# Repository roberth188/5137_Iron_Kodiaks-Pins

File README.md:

# 5137_Iron_Kodiaks-Pins
The team circuit board pins files, including both the schematic/board and Gerber files.
Contact me if you have any questions.

To order new boards, go to [dirtyPCBs](http://dirtypcbs.com/) and upload all of the Gerber files (the files that don't end in either .sch or .brd. Make sure to select 2 layer, the 5x5 cm size, the proper quantity, red color, 1.6mm thickness, ENIG Coating, no stencil, Regular processing, shipping to United States, and DHL China works very well. This will make the boards exactly like they were ordered before. 

Contact me about ordering the components - they vary considerably with what is in stock, so they will need to be found again.

Board file images were rendered with the fabulous ZofzPCB tool (available free online) and the colors were adjusted to accurately represent the ENIG plating over the pads of the red PCBS (for the team's cardinal and gold colors).

</img> </img> 

Yes, the trace that goes through the switch in that pad is unintentional but, as that connection is shorted, anyways, when it is turned off, it electrically has no impact. It can be safely and completely ignored.

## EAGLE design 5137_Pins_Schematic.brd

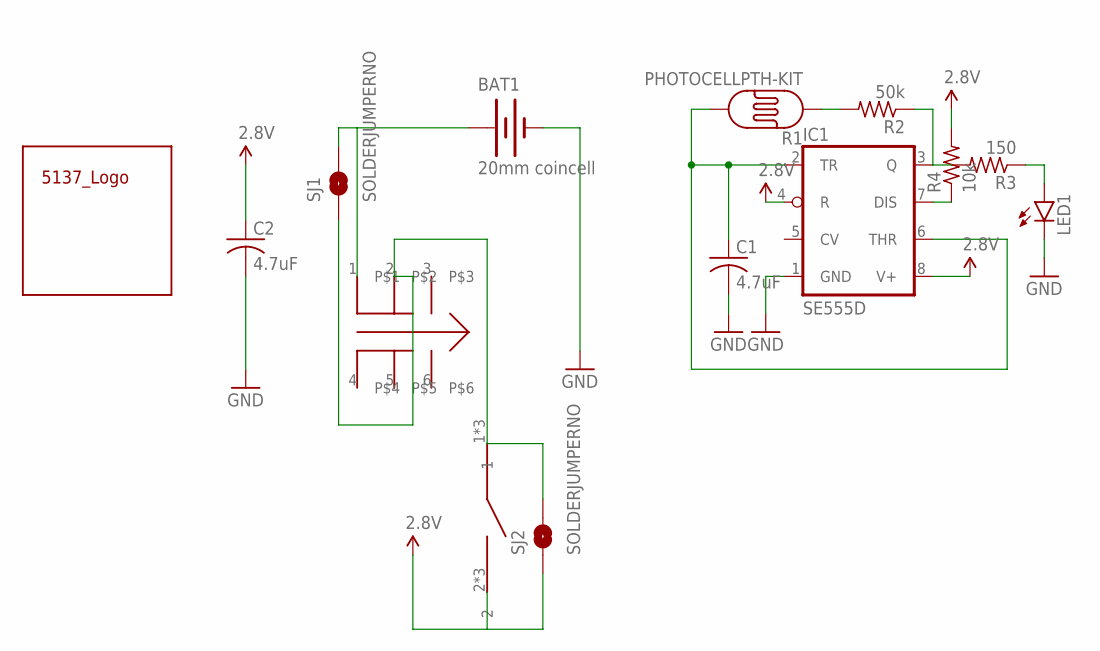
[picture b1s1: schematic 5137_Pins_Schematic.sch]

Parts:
BAT1: 20mm coincell; BATTCON_20MM_4LEGS
C1, C2: 4.7uF; C1206K
IC1: SE555D; SO08
LED1: LED5MM-KIT
R1: PHOTOCELLPTH-KIT; PHOTOCELL-KIT
R2: 50k; R1206W
R3: 150; R1206W
R4: 10k; R1206W
SJ1, SJ2: SOLDERJUMPERNO; SJ_2S-NO
U$1: 5137_LOGO_DEV; 5137_LOGO_PKG
U$2: SAFETY_PIN_SWITCH
U$3: DPDT_GULL_WING_SWITCH

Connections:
2.8V: C2.1, IC1.4 (R), IC1.8 (V+), R4.2, SJ2.1, U$2.2, U$2.2A (2), U$2.2B (2)
GND: BAT1.2 (-), C1.2, C2.2, IC1.1 (GND), LED1.K (C)
unnamed: IC1.3 (Q), R2.1, R3.2
unnamed: LED1.A, R3.1
unnamed: IC1.7 (DIS), R4.1
unnamed: R1.1, R2.2
unnamed: C1.1, IC1.2 (TR), IC1.6 (THR), R1.2
unnamed: BAT1.1 (+), SJ1.2, U$3.1
unnamed: SJ1.1, SJ2.2, U$2.1, U$2.1A (1), U$2.1B (1), U$3.2

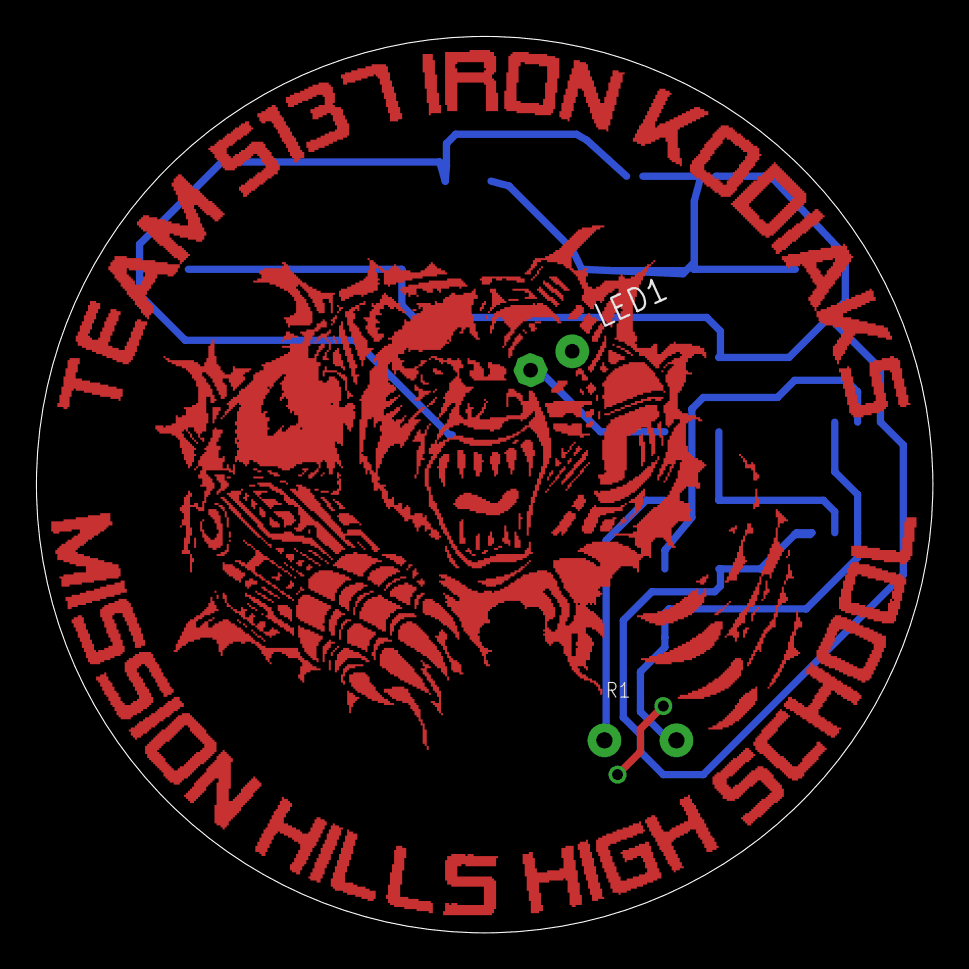
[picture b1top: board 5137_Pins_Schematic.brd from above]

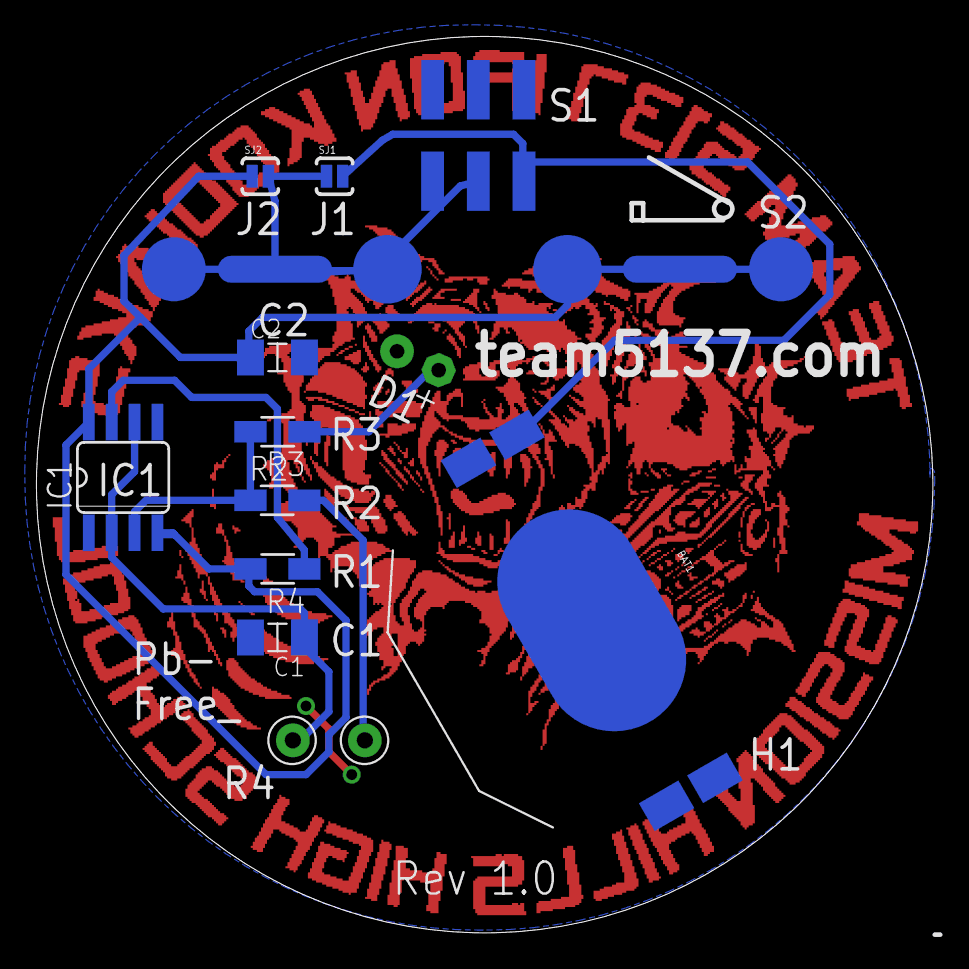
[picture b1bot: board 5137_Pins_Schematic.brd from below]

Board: 2 copper layers, 49.8 x 49.8 mm, 14 parts (11 on the bottom side), 9 nets.

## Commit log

2015-11-15 :space_invader: Added .gitattributes & .gitignore files
2015-11-15 Board_files
2015-11-15 Images
2015-11-15 Added .sch and .brd files
    All are now added

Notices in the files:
parts and their libraries:
SparkFun-Sensors: Licensing: Creative Commons ShareAlike 4.0 International - https://creativecommons.org/licenses/by-sa/4.0
